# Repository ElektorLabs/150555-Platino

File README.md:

# 150555-Platino
Arduino compatible universal AVR board for 28-pin and 40-pin ATmega devices.

Platino is a board that address the ever returning problem of adding a user interface to a project. With 
Platino this is solved so that you can concentrate on your application instead of fiddling with low-level
drivers for user interfacing.

To achieve this Platino features footprints for pushbuttons, rotary encoders, a buzzer, an (RGB) LED, and an
LCD. Pushbuttons and rotary encoders have a flexible layout allowing a user interface adapted to the applications.
Platino supports 2 lines by 16 characters (2x16), 4x16 and 4x20 LCDs.

An Arduino library/core is available that contains drivers for all the peripherals, making programming easy.
Don't worry about debouncing pushbuttons, controlling LCDs or reading rotary encoders, the library handles it all
for you.

For even more flexibility Platino has solder jumpers to configure the board, allowing peripherals to be connected
to different ports.

Platino supports the following MCUs:
- ATmega8
- ATmega16
- ATmega32
- ATmega48 (not supported in Arduino IDE)
- ATmega88
- ATmega164
- ATmega168
- ATmega324
- ATmega328
- ATmega644
- ATmega1284

Arduino compatible bootloaders for all supported processors (except ATmega48) are available too.

For easy installation Platino is contained in a Board Package for the Arduino IDE, see https://github.com/ElektorLabs/Arduino

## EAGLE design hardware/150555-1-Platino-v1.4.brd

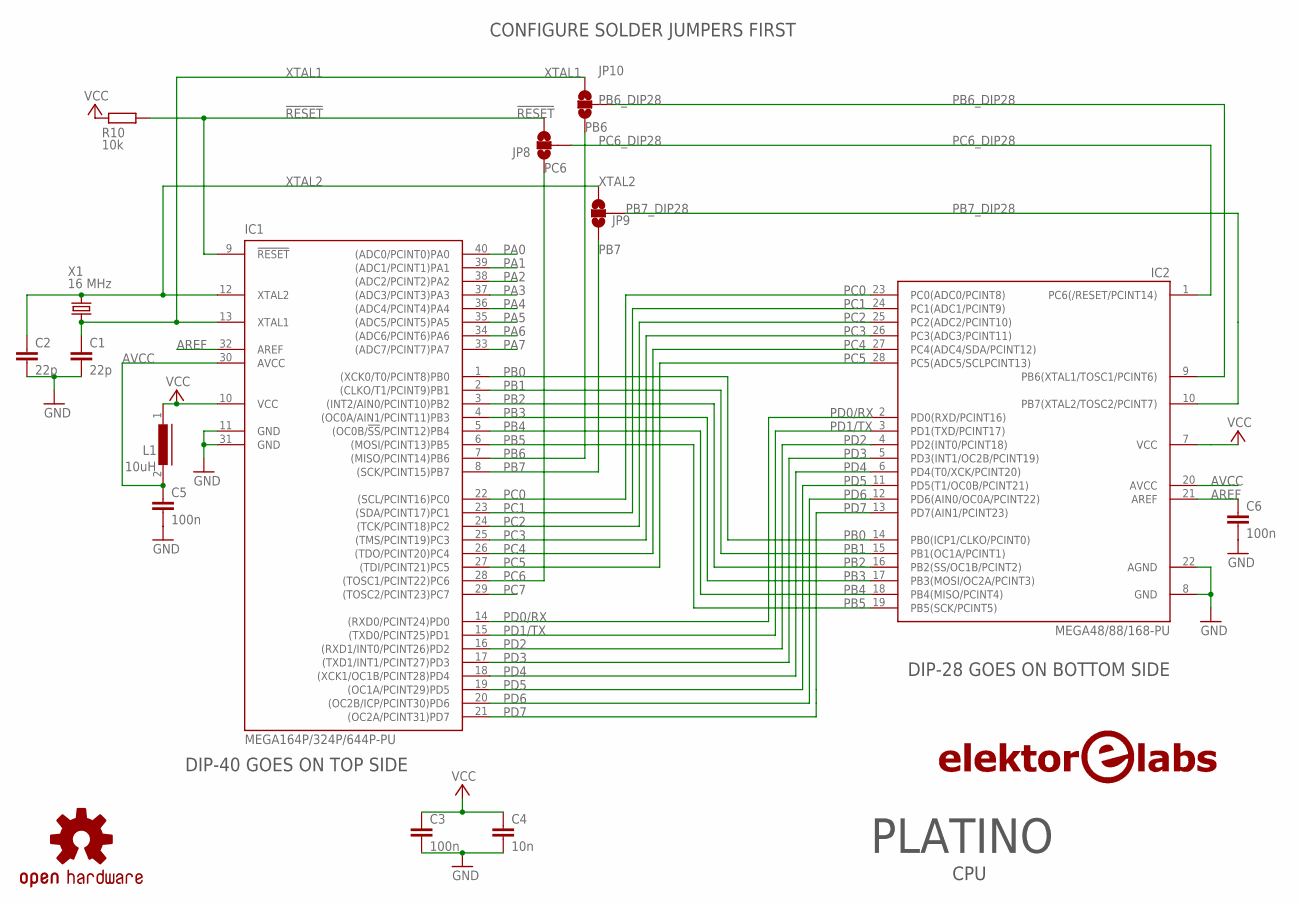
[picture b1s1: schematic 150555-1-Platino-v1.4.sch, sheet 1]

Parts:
C1, C2: 22p; ELPP-CNP-250
C3, C5, C6: 100n; ELPP-CNP-508
C4: 10n; ELPP-CNP-254
IC1: MEGA164P/324P/644P-PU; DIL40
IC2: MEGA48/88/168-PU; DIL28-3
JP8, JP9, JP10: SOLDERJUMPER_2WAYT; SJ_2
L1: 10uH; ELPP-L-0207-1000
LOGO2: LOGO-ELEKTOR-LABS-25MM; EPP-LOGO-ELEKTOR-LABS-25MM
R10: 10k; ELPP-R-0207-1000
U$2: OSHW-LOGOM; OSHW-LOGO-M
X1: 16 MHz; ELPP-HC49

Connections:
!RESET: IC1.9 (!RESET), JP8.3, R10.1; also elsewhere on the board
AREF: C6.1, IC1.32 (AREF), IC2.21 (AREF); also elsewhere on the board
AVCC: C5.1, IC1.30 (AVCC), IC2.20 (AVCC), L1.2
GND: C1.2, C2.2, C3.2, C4.2, C5.2, C6.2, IC1.11 (GND), IC1.31 (GND), IC2.8 (GND), IC2.22 (AGND); also elsewhere on the board
PA0: IC1.40 ((ADC0/PCINT0)PA0); also elsewhere on the board
PA1: IC1.39 ((ADC1/PCINT1)PA1); also elsewhere on the board
PA2: IC1.38 ((ADC2/PCINT2)PA2); also elsewhere on the board
PA3: IC1.37 ((ADC3/PCINT3)PA3); also elsewhere on the board
PA4: IC1.36 ((ADC4/PCINT4)PA4); also elsewhere on the board
PA5: IC1.35 ((ADC5/PCINT5)PA5); also elsewhere on the board
PA6: IC1.34 ((ADC6/PCINT6)PA6); also elsewhere on the board
PA7: IC1.33 ((ADC7/PCINT7)PA7); also elsewhere on the board
PB0: IC1.1 ((XCK0/T0/PCINT8)PB0), IC2.14 (PB0(ICP1/CLKO/PCINT0)); also elsewhere on the board
PB1: IC1.2 ((CLKO/T1/PCINT9)PB1), IC2.15 (PB1(OC1A/PCINT1)); also elsewhere on the board
PB2: IC1.3 ((INT2/AIN0/PCINT10)PB2), IC2.16 (PB2(SS/OC1B/PCINT2)); also elsewhere on the board
PB3: IC1.4 ((OC0A/AIN1/PCINT11)PB3), IC2.17 (PB3(MOSI/OC2A/PCINT3)); also elsewhere on the board
PB4: IC1.5 ((OC0B/!SS!/PCINT12)PB4), IC2.18 (PB4(MISO/PCINT4)); also elsewhere on the board
PB5: IC1.6 ((MOSI/PCINT13)PB5), IC2.19 (PB5(SCK/PCINT5)); also elsewhere on the board
PB6: IC1.7 ((MISO/PCINT14)PB6), JP10.1; also elsewhere on the board
PB6_DIP28: IC2.9 (PB6(XTAL1/TOSC1/PCINT6)), JP10.2
PB7: IC1.8 ((SCK/PCINT15)PB7), JP9.1; also elsewhere on the board
PB7_DIP28: IC2.10 (PB7(XTAL2/TOSC2/PCINT7)), JP9.2
PC0: IC1.22 ((SCL/PCINT16)PC0), IC2.23 (PC0(ADC0/PCINT8)); also elsewhere on the board
PC1: IC1.23 ((SDA/PCINT17)PC1), IC2.24 (PC1(ADC1/PCINT9)); also elsewhere on the board
PC2: IC1.24 ((TCK/PCINT18)PC2), IC2.25 (PC2(ADC2/PCINT10)); also elsewhere on the board
PC3: IC1.25 ((TMS/PCINT19)PC3), IC2.26 (PC3(ADC3/PCINT11)); also elsewhere on the board
PC4: IC1.26 ((TDO/PCINT20)PC4), IC2.27 (PC4(ADC4/SDA/PCINT12)); also elsewhere on the board
PC5: IC1.27 ((TDI/PCINT21)PC5), IC2.28 (PC5(ADC5/SCLPCINT13)); also elsewhere on the board
PC6: IC1.28 ((TOSC1/PCINT22)PC6), JP8.1; also elsewhere on the board
PC6_DIP28: IC2.1 (PC6(/RESET/PCINT14)), JP8.2
PC7: IC1.29 ((TOSC2/PCINT23)PC7); also elsewhere on the board
PD0/RX: IC1.14 ((RXD0/PCINT24)PD0), IC2.2 (PD0(RXD/PCINT16)); also elsewhere on the board
PD1/TX: IC1.15 ((TXD0/PCINT25)PD1), IC2.3 (PD1(TXD/PCINT17)); also elsewhere on the board
PD2: IC1.16 ((RXD1/INT0/PCINT26)PD2), IC2.4 (PD2(INT0/PCINT18)); also elsewhere on the board
PD3: IC1.17 ((TXD1/INT1/PCINT27)PD3), IC2.5 (PD3(INT1/OC2B/PCINT19)); also elsewhere on the board
PD4: IC1.18 ((XCK1/OC1B/PCINT28)PD4), IC2.6 (PD4(T0/XCK/PCINT20)); also elsewhere on the board
PD5: IC1.19 ((OC1A/PCINT29)PD5), IC2.11 (PD5(T1/OC0B/PCINT21)); also elsewhere on the board
PD6: IC1.20 ((OC2B/ICP/PCINT30)PD6), IC2.12 (PD6(AIN0/OC0A/PCINT22)); also elsewhere on the board
PD7: IC1.21 ((OC2A/PCINT31)PD7), IC2.13 (PD7(AIN1/PCINT23)); also elsewhere on the board
VCC: C3.1, C4.1, IC1.10 (VCC), IC2.7 (VCC), L1.1, R10.2; also elsewhere on the board
XTAL1: C1.1, IC1.13 (XTAL1), JP10.3, X1.1
XTAL2: C2.1, IC1.12 (XTAL2), JP9.3, X1.2

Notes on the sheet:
CPU
CONFIGURE SOLDER JUMPERS FIRST
DIP-40 GOES ON TOP SIDE
DIP-28 GOES ON BOTTOM SIDE
PLATINO

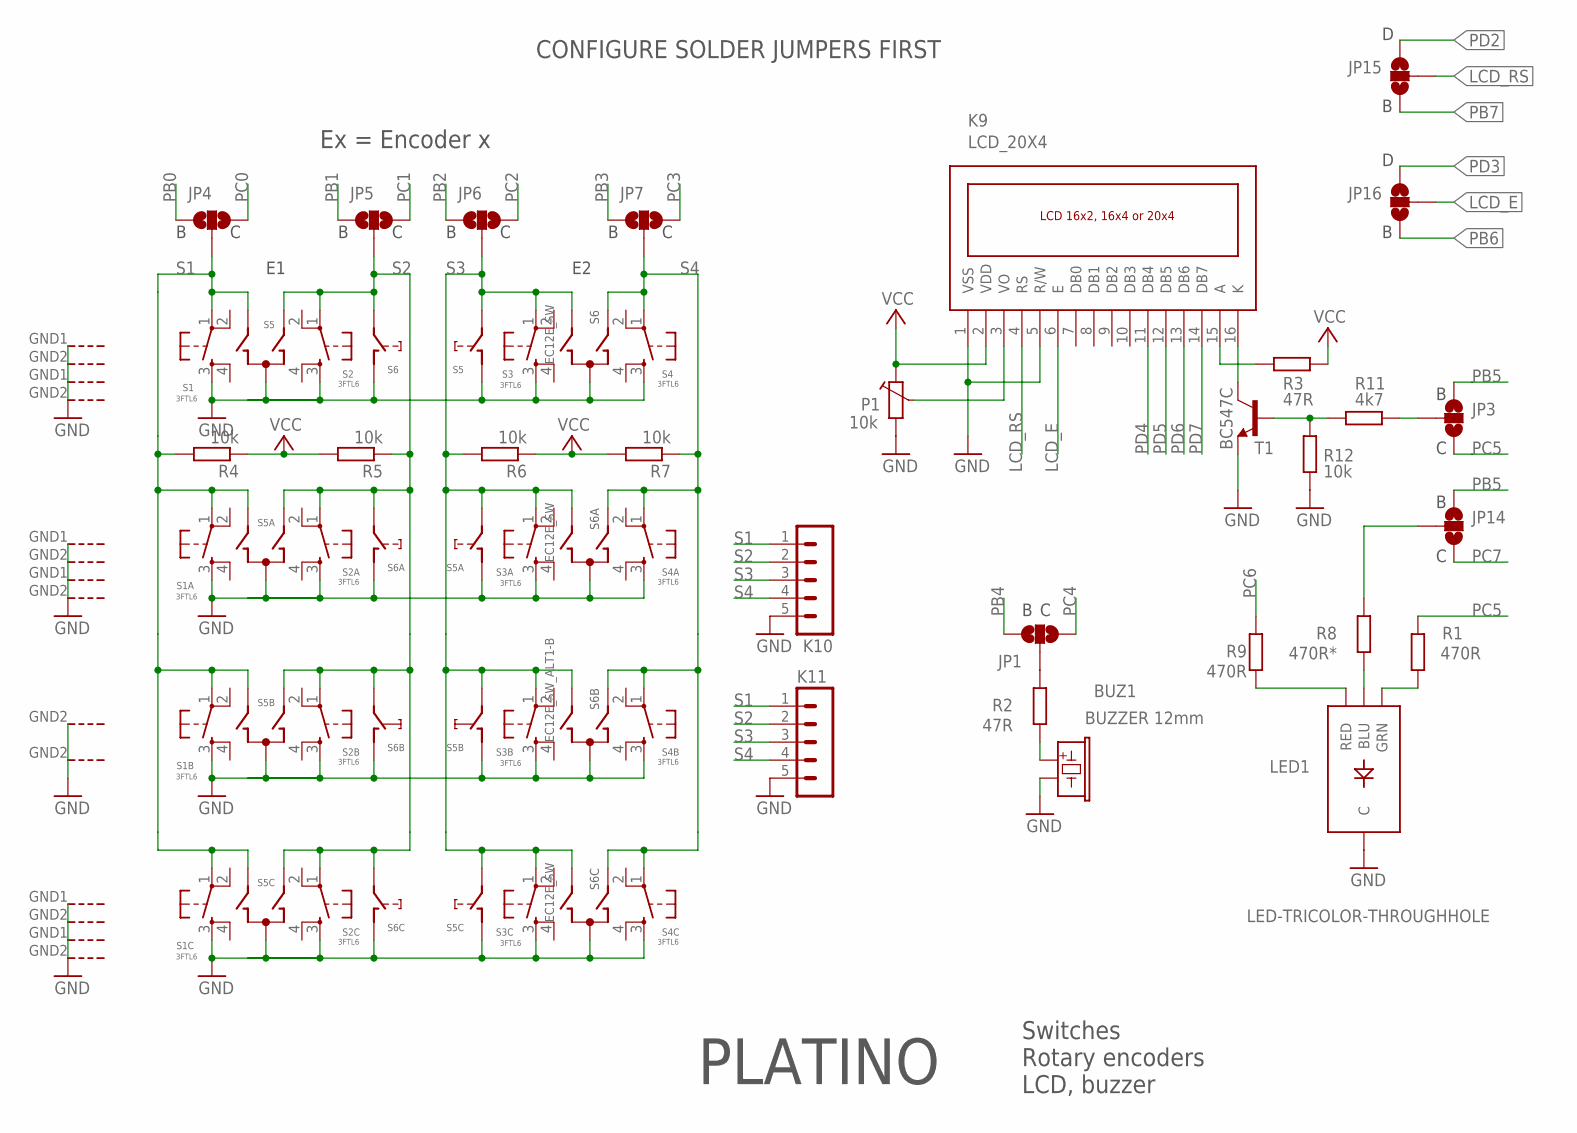
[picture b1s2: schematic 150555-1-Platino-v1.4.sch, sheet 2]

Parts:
BUZ1: BUZZER 12mm; ELPP-BUZZER-12MM
JP1, JP3, JP4, JP5, JP6, JP7, JP14, JP15, JP16: SOLDERJUMPER_2WAYT; SJ_2
K9: LCD_20X4; LCD_MULTI2
K10, K11: K-HEADER-MALE-1X5-V; ELPP-SIL-M-5-WAY
LED1: LED-TRICOLOR-THROUGHHOLE
P1: 10k; ELPP-TRIMMER-CB10-H
R1, R9: 470R; ELPP-R-0207-1000
R2, R3: 47R; ELPP-R-0207-1000
R4, R5, R6, R7, R12: 10k; ELPP-R-0207-1000
R8: 470R*; ELPP-R-0207-1000
R11: 4k7; ELPP-R-0207-1000
S1, S1A, S1B, S1C, S2, S2A, S2B, S2C, S3, S3A, S3B, S3C, S4, S4A, S4B, S4C: 3FTL6; PUSHBUTTON_MULTIMEC
S5, S5A, S5C, S6, S6A, S6C: EC12E_SW; ALPS_EC12E_SW
S5B, S6B: EC12E_SW_ALT1-B; ALPS_EC12E_SW_ALT2
T1: BC547C; TO-92

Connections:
BLUE: LED1.BLU, R8.1
GATE: JP3.2, R11.2
GND: BUZ1.- (2), K9.1 (VSS), K9.5 (R/W), K10.5, K11.5, LED1.GND (C), P1.1, R12.1, S1.3, S1A.3, S1B.3, S1C.3, S2.3, S2A.3, S2B.3, S2C.3, S3.3, S3A.3, S3B.3, S3C.3, S4.3, S4A.3, S4B.3, S4C.3, S5.C, S5.D (1), S5.GND1 (G), S5.GND2 (G), S5A.C, S5A.D (1), S5A.GND1 (G), S5A.GND2 (G), S5B.C, S5B.D (1), S5B.GND2 (G), S5C.C, S5C.D (1), S5C.GND1 (G), S5C.GND2 (G), S6.C, S6.D (1), S6.GND1 (G), S6.GND2 (G), S6A.C, S6A.D (1), S6A.GND1 (G), S6A.GND2 (G), S6B.C, S6B.D (1), S6B.GND2 (G), S6C.C, S6C.D (1), S6C.GND1 (G), S6C.GND2 (G), T1.1 (E); also elsewhere on the board
GREEN: LED1.GRN, R1.1
LCD_BL_A: K9.15 (A), R3.1
LCD_BL_K: K9.16 (K), T1.3 (C)
LCD_E: JP16.2, K9.6 (E)
LCD_RS: JP15.2, K9.4 (RS)
LCD_VO: K9.3 (VO), P1.3
unnamed: BUZ1.+ (1), R2.1
unnamed: R11.1, R12.2, T1.2 (B)
unnamed: JP1.2, R2.2
unnamed: JP14.2, R8.2
PB0: JP4.1; also elsewhere on the board
PB1: JP5.1; also elsewhere on the board
PB2: JP6.1; also elsewhere on the board
PB3: JP7.1; also elsewhere on the board
PB4: JP1.1; also elsewhere on the board
PB5: JP3.3, JP14.3; also elsewhere on the board
PB6: JP16.1; also elsewhere on the board
PB7: JP15.1; also elsewhere on the board
PC0: JP4.3; also elsewhere on the board
PC1: JP5.3; also elsewhere on the board
PC2: JP6.3; also elsewhere on the board
PC3: JP7.3; also elsewhere on the board
PC4: JP1.3; also elsewhere on the board
PC5: JP3.1, R1.2; also elsewhere on the board
PC6: R9.2; also elsewhere on the board
PC7: JP14.1; also elsewhere on the board
PD2: JP15.3; also elsewhere on the board
PD3: JP16.3; also elsewhere on the board
PD4: K9.11 (DB4); also elsewhere on the board
PD5: K9.12 (DB5); also elsewhere on the board
PD6: K9.13 (DB6); also elsewhere on the board
PD7: K9.14 (DB7); also elsewhere on the board
RED: LED1.RED, R9.1
S1: JP4.2, K10.1, K11.1, R4.2, S1.1, S1A.1, S1B.1, S1C.1, S5.B, S5A.B, S5B.B, S5C.B
S2: JP5.2, K10.2, K11.2, R5.1, S2.1, S2A.1, S2B.1, S2C.1, S5.A, S5A.A, S5B.A, S5C.A, S6.E (2), S6A.E (2), S6B.E (2), S6C.E (2)
S3: JP6.2, K10.3, K11.3, R6.2, S3.1, S3A.1, S3B.1, S3C.1, S5.E (2), S5A.E (2), S5B.E (2), S5C.E (2), S6.B, S6A.B, S6B.B, S6C.B
S4: JP7.2, K10.4, K11.4, R7.1, S4.1, S4A.1, S4B.1, S4C.1, S6.A, S6A.A, S6B.A, S6C.A
VCC: K9.2 (VDD), P1.2, R3.2, R4.1, R5.2, R6.1, R7.2; also elsewhere on the board

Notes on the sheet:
Switches
Rotary encoders
LCD, buzzer
CONFIGURE SOLDER JUMPERS FIRST
PLATINO
Ex = Encoder x

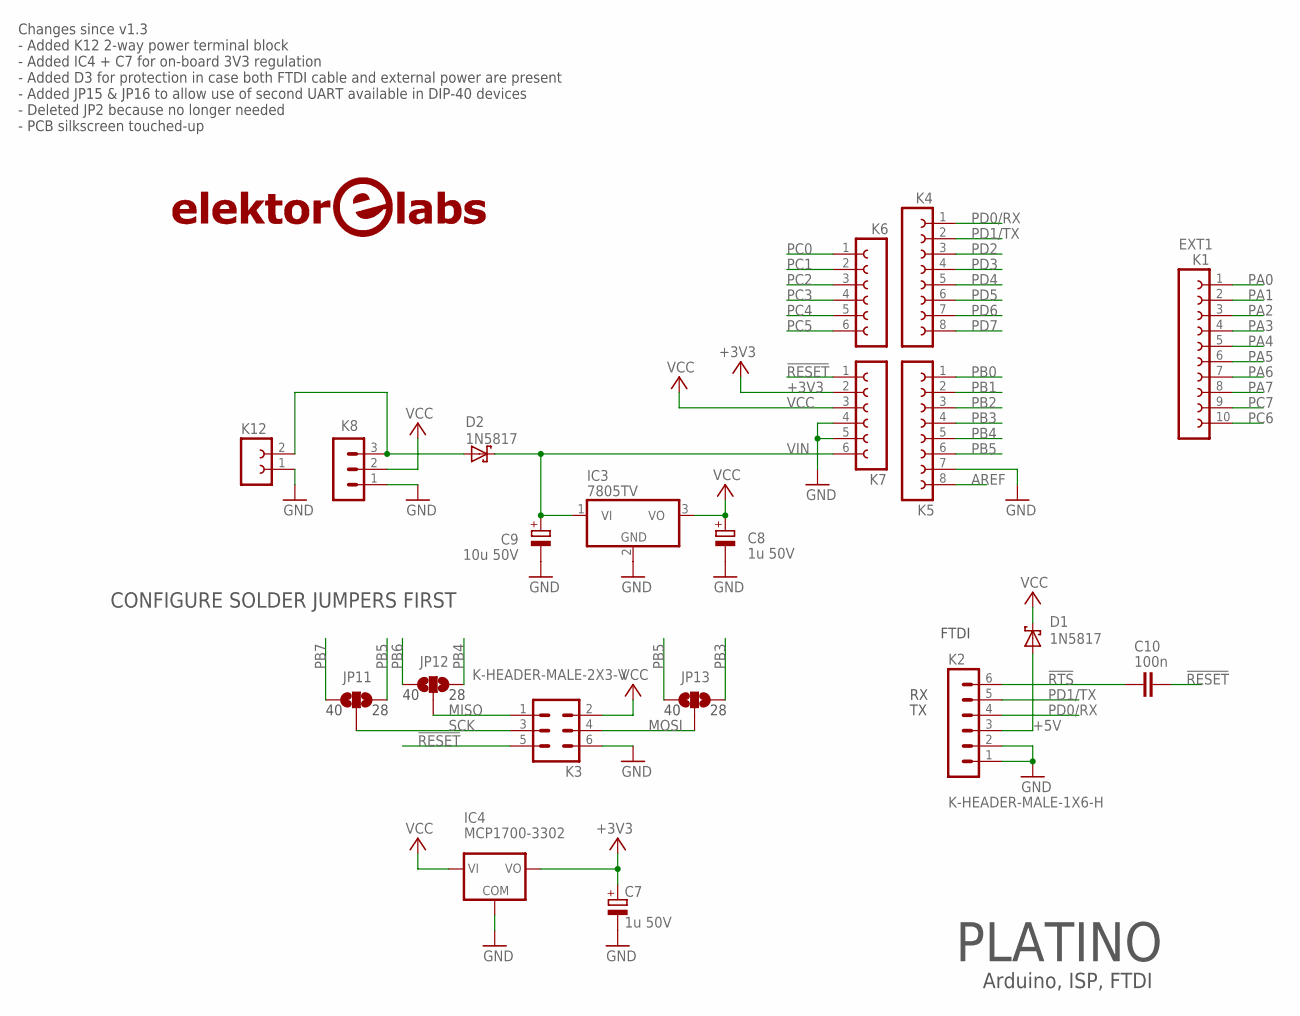
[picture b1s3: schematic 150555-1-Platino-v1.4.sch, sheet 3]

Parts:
C7, C8: 1u 50V; ELPP-CP-200-500
C9: 10u 50V; ELPP-CP-200-500
C10: 100n; ELPP-CNP-508
D1, D2: 1N5817; ELPP-DO-41
IC3: 7805TV; TO220V
IC4: MCP1700-3302; ELPP-TO-92
JP11, JP12, JP13: SOLDERJUMPER_2WAYT; SJ_2
K1: EXT1; ELPP-SIL-F-10-WAY
K2: K-HEADER-MALE-1X6-H; ELPP-SIL-M-6-WAY-90DEG
K3: K-HEADER-MALE-2X3-V; ELPP-DIL-M-6-WAY-V
K4, K5: K-HEADER-FEMALE-1X8-V; ELPP-SIL-F-8-WAY
K6, K7: K-HEADER-FEMALE-1X6-V; ELPP-SIL-F-6-WAY
K8: K-HEADER-MALE-1X3-V; ELPP-SIL-M-3-WAY
K12: K-TERMINAL-BLOCK-1X2-350; ELPP-TB-350-2
LOGO1: LOGO-ELEKTOR-LABS-25MM; EPP-LOGO-ELEKTOR-LABS-25MM

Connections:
!RESET: C10.2, K3.5, K7.1; also elsewhere on the board
!RTS: C10.1, K2.6
+3V3: C7.+, IC4.3 (VO), K7.2
+5V: D1.A, K2.3
AREF: K5.8; also elsewhere on the board
GND: C7.-, C8.-, C9.-, IC3.2 (GND), IC4.1 (COM), K2.1, K2.2, K3.6, K5.7, K7.4, K7.5, K8.1, K12.1; also elsewhere on the board
MISO: JP12.2, K3.1
MOSI: JP13.2, K3.4
unnamed: D2.A, K8.3, K12.2
PA0: K1.1; also elsewhere on the board
PA1: K1.2; also elsewhere on the board
PA2: K1.3; also elsewhere on the board
PA3: K1.4; also elsewhere on the board
PA4: K1.5; also elsewhere on the board
PA5: K1.6; also elsewhere on the board
PA6: K1.7; also elsewhere on the board
PA7: K1.8; also elsewhere on the board
PB0: K5.1; also elsewhere on the board
PB1: K5.2; also elsewhere on the board
PB2: K5.3; also elsewhere on the board
PB3: JP13.3, K5.4; also elsewhere on the board
PB4: JP12.3, K5.5; also elsewhere on the board
PB5: JP11.3, JP13.1, K5.6; also elsewhere on the board
PB6: JP12.1; also elsewhere on the board
PB7: JP11.1; also elsewhere on the board
PC0: K6.1; also elsewhere on the board
PC1: K6.2; also elsewhere on the board
PC2: K6.3; also elsewhere on the board
PC3: K6.4; also elsewhere on the board
PC4: K6.5; also elsewhere on the board
PC5: K6.6; also elsewhere on the board
PC6: K1.10; also elsewhere on the board
PC7: K1.9; also elsewhere on the board
PD0/RX: K2.4, K4.1; also elsewhere on the board
PD1/TX: K2.5, K4.2; also elsewhere on the board
PD2: K4.3; also elsewhere on the board
PD3: K4.4; also elsewhere on the board
PD4: K4.5; also elsewhere on the board
PD5: K4.6; also elsewhere on the board
PD6: K4.7; also elsewhere on the board
PD7: K4.8; also elsewhere on the board
SCK: JP11.2, K3.3
VCC: C8.+, D1.C, IC3.3 (VO), IC4.2 (VI), K3.2, K7.3, K8.2; also elsewhere on the board
VIN: C9.+, D2.C, IC3.1 (VI), K7.6

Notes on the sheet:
Arduino, ISP, FTDI
FTDI
CONFIGURE SOLDER JUMPERS FIRST
PLATINO
Changes since v1.3 - Added K12 2-way power terminal block - Added IC4 + C7 for on-board 3V3 regulation - Added D3 for protection in case both FTDI cable and external power are present - Added JP15 & JP16 to allow use of second UART available in DIP-40 devices - Deleted JP2 because no longer needed 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

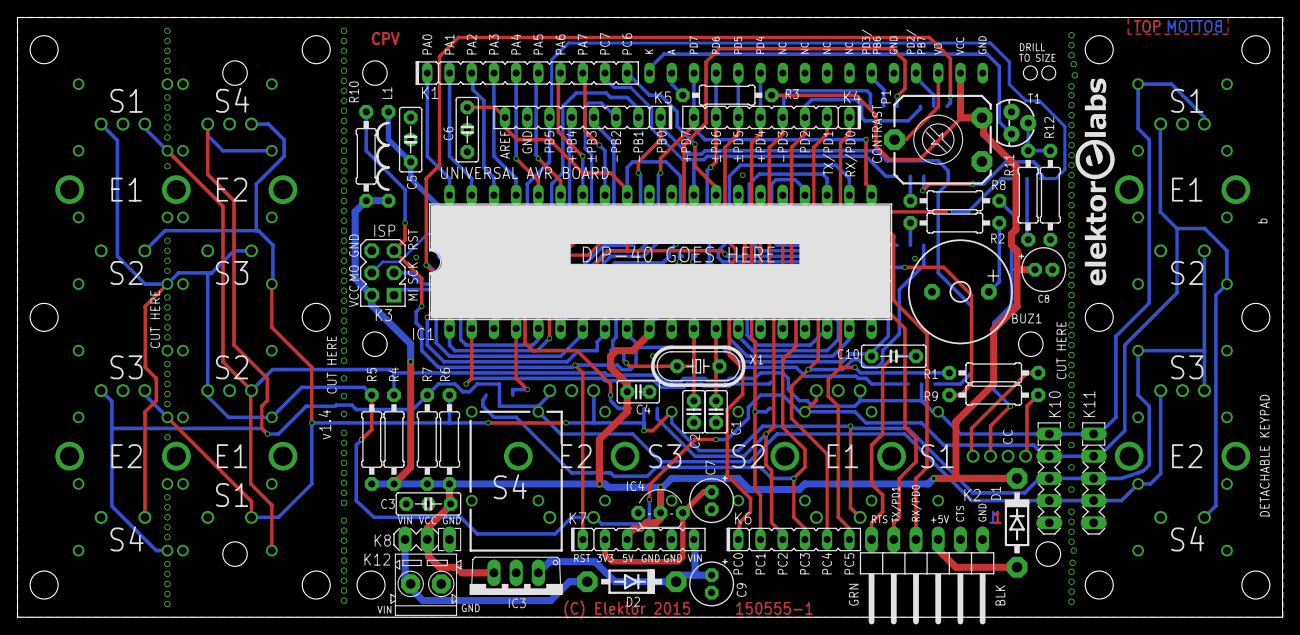
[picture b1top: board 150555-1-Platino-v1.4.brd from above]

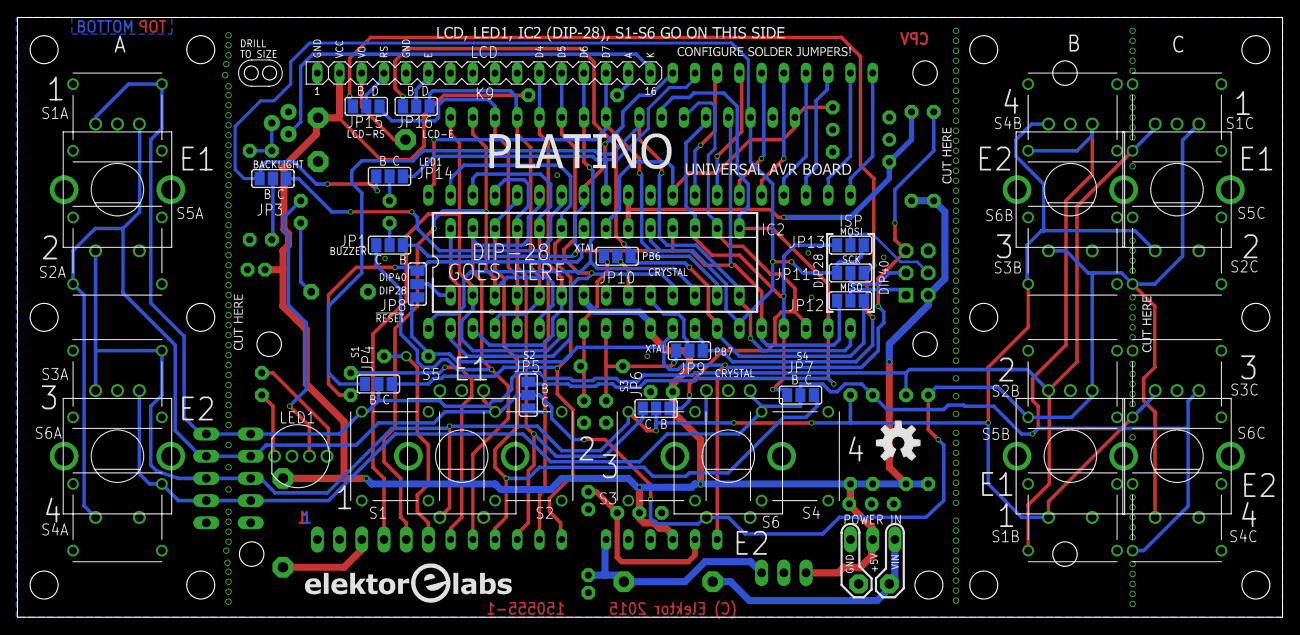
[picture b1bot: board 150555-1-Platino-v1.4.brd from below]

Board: 2 copper layers, 144.7 x 68.6 mm, 88 parts (44 on the bottom side), 67 nets.

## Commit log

2015-10-27 :circus_tent: Added .gitattributes & .gitignore files
2015-10-28 Added exemple
2015-11-06 Release
    Fixed all OAR and hole-in-hole issues.
    Minor silkscreen edits.
2015-11-06 Added note for ATmega48

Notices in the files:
hardware/150555-1-Platino-v1.4.brd:
COPYRIGHT: (C) Elektor 2015
parts and their libraries:
SparkFun-Aesthetics: Licensing: CC v3.0 Share-Alike You are welcome to use this library for commercial purposes.
